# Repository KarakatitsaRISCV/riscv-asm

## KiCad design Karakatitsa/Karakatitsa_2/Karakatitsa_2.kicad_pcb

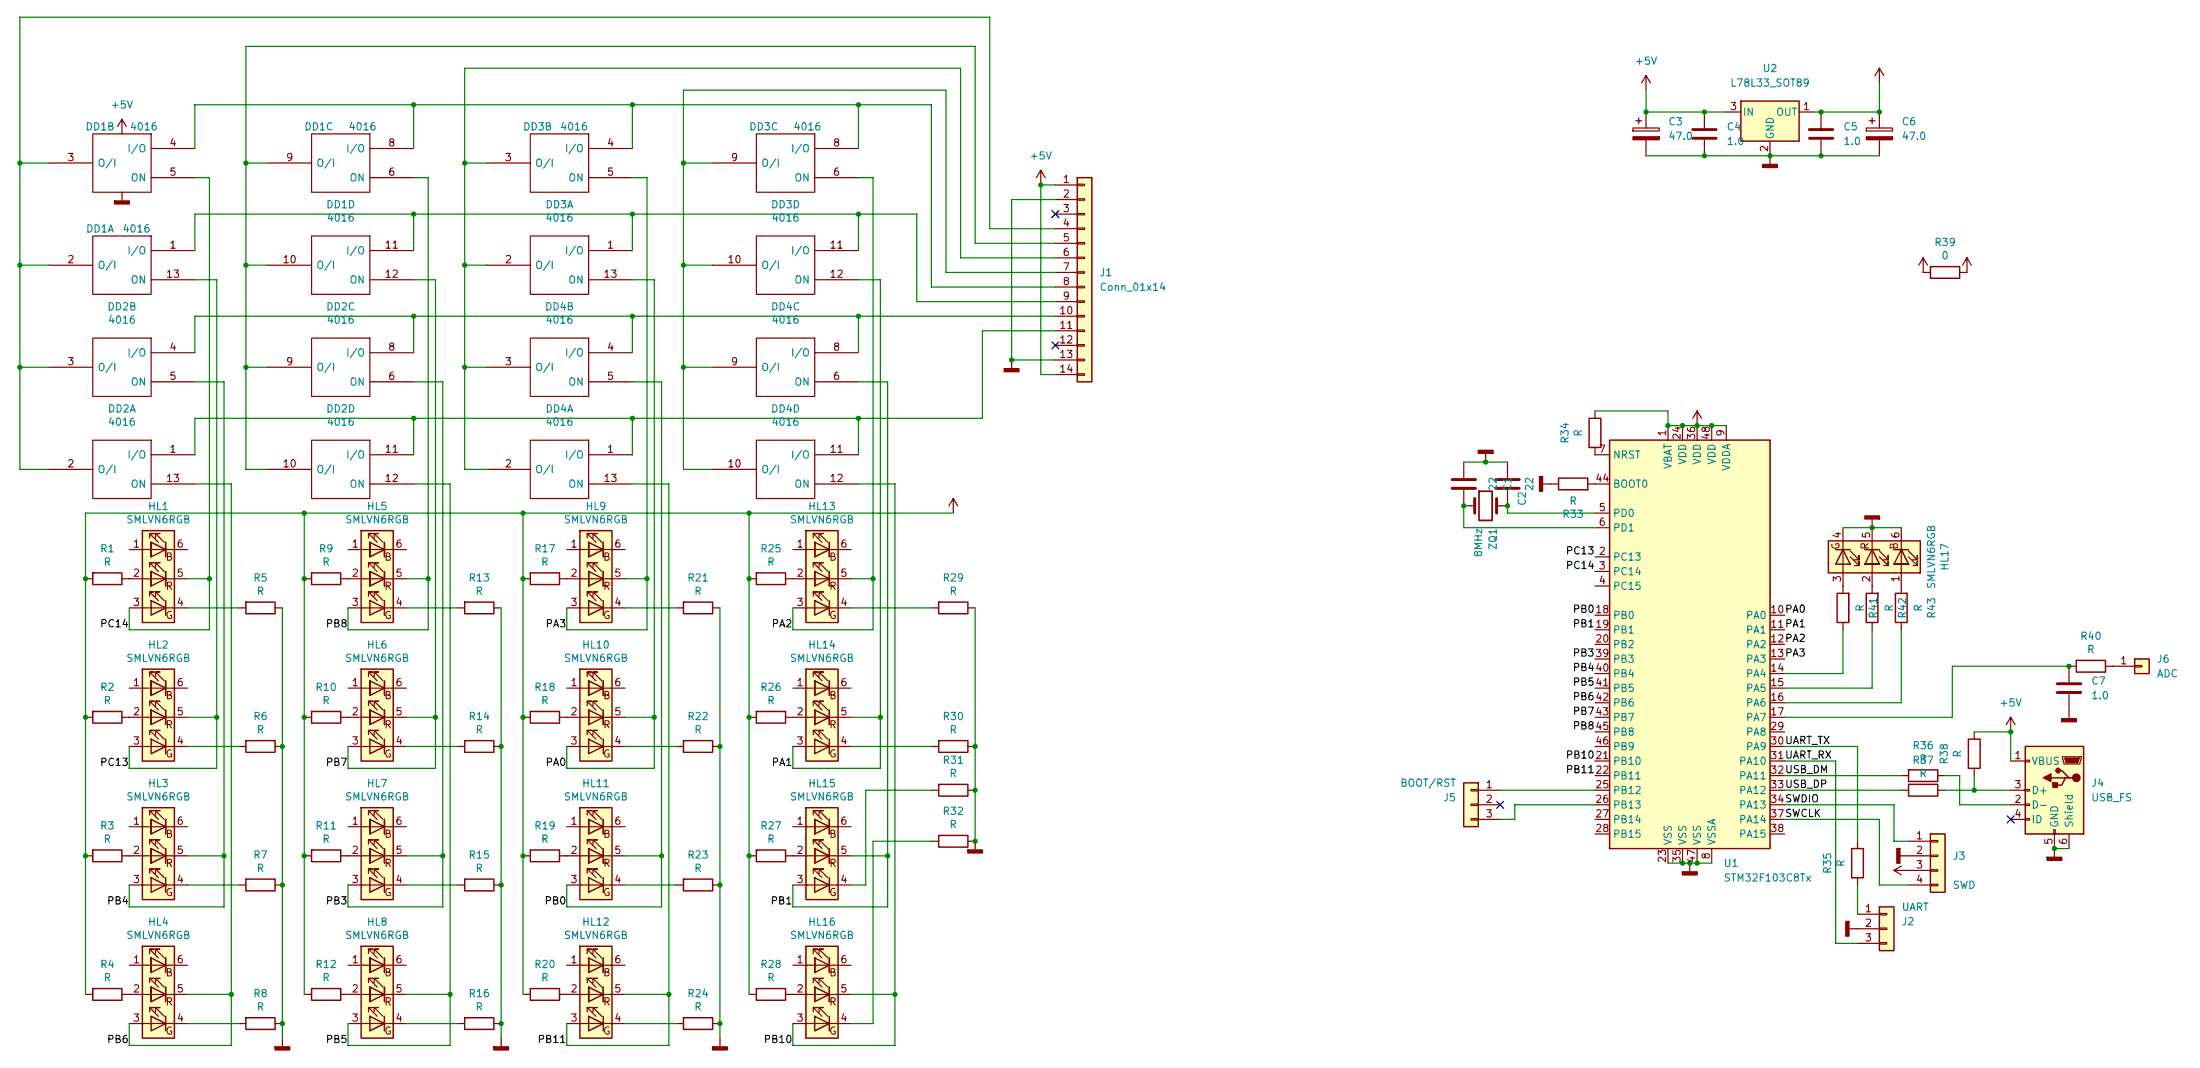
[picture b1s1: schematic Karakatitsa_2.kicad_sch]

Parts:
C1, C2: 22; C_Disc_D5.0mm_W2.5mm_P2.50mm
C3, C6: 47.0; CP_Radial_D6.3mm_P2.50mm
C4, C5, C7: 1.0; C_Disc_D7.5mm_W2.5mm_P5.00mm
DD1, DD2, DD3, DD4: 4016; DIP-14_W7.62mm_LongPads
HL1, HL2, HL3, HL4, HL5, HL6, HL7, HL8, HL9, HL10, HL11, HL12, HL13, HL14, HL15, HL16, HL17: SMLVN6RGB; LED_RGB_Cree-PLCC-6_6x5mm_P2.1mm
J1: Conn_01x14; PinSocket_1x14_P2.54mm_Horizontal
J2: UART; PinHeader_1x03_P2.54mm_Horizontal
J3: SWD; PinHeader_1x04_P2.54mm_Vertical
J4: USB_FS; USB-mini
J5: BOOT/RST; PinHeader_1x03_P2.54mm_Horizontal
J6: ADC; PinHeader_1x01_P2.54mm_Horizontal
R1, R2, R3, R4, R5, R6, R7, R8, R9, R10, R11, R12, R13, R14, R15, R16, R17, R18, R19, R20, R21, R22, R23, R24, R25, R26, R27, R28, R29, R30, R31, R32, R33, R34, R35, R36, R37, R38, R40, R41, R42, R43: R; R_0805_2012Metric
R39: 0; R_0805_2012Metric
U1: STM32F103C8Tx; LQFP-48_7x7mm_P0.5mm
U2: L78L33_SOT89; SOT-89-3
ZQ1: 8MHz; Crystal_HC49-4H_Vertical

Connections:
+5V: C3.1, C4.1, DD1.14 (Vdd), DD2.14 (Vdd), DD3.14 (Vdd), DD4.14 (Vdd), J1.1, J1.14, J4.1 (VBUS), R38.1, U2.3 (IN)
/PA0: DD3.13 (ON), HL10.3 (GA), HL10.5 (RK), U1.10 (PA0)
/PA1: DD3.12 (ON), HL14.3 (GA), HL14.5 (RK), U1.11 (PA1)
/PA2: DD3.6 (ON), HL13.3 (GA), HL13.5 (RK), U1.12 (PA2)
/PA3: DD3.5 (ON), HL9.3 (GA), HL9.5 (RK), U1.13 (PA3)
/PB0: DD4.5 (ON), HL11.3 (GA), HL11.5 (RK), U1.18 (PB0)
/PB1: DD4.6 (ON), HL15.3 (GA), HL15.5 (RK), U1.19 (PB1)
/PB3: DD2.6 (ON), HL7.3 (GA), HL7.5 (RK), U1.39 (PB3)
/PB4: DD2.5 (ON), HL3.3 (GA), HL3.5 (RK), U1.40 (PB4)
/PB5: DD2.12 (ON), HL8.3 (GA), HL8.5 (RK), U1.41 (PB5)
/PB6: DD2.13 (ON), HL4.3 (GA), HL4.5 (RK), U1.42 (PB6)
/PB7: DD1.12 (ON), HL6.3 (GA), HL6.5 (RK), U1.43 (PB7)
/PB8: DD1.6 (ON), HL5.3 (GA), HL5.5 (RK), U1.45 (PB8)
/PB10: DD4.12 (ON), HL16.3 (GA), HL16.5 (RK), U1.21 (PB10)
/PB11: DD4.13 (ON), HL12.3 (GA), HL12.5 (RK), U1.22 (PB11)
/PC13: DD1.13 (ON), HL2.3 (GA), HL2.5 (RK), U1.2 (PC13)
/PC14: DD1.5 (ON), HL1.3 (GA), HL1.5 (RK), U1.3 (PC14)
/SWCLK: J3.4, U1.37 (PA14)
/SWDIO: J3.1, U1.34 (PA13)
/UART_RX: J2.3, U1.31 (PA10)
/UART_TX: R35.1, U1.30 (PA9)
/USB_DM: R36.2, U1.32 (PA11)
/USB_DP: R37.2, U1.33 (PA12)
GNDD: C1.1, C2.1, C3.2, C4.2, C5.2, C6.2, C7.2, DD1.7 (Vss), DD2.7 (Vss), DD3.7 (Vss), DD4.7 (Vss), HL17.4 (GK), HL17.5 (RK), HL17.6 (BK), J1.2, J1.13, J2.2, J3.2, J4.5 (GND), J4.6 (Shield), R5.1, R6.1, R7.1, R8.1, R13.1, R14.1, R15.1, R16.1, R21.1, R22.1, R23.1, R24.1, R29.1, R30.1, R31.1, R32.1, R33.1, U1.8 (VSSA), U1.23 (VSS), U1.35 (VSS), U1.47 (VSS), U2.2 (GND)
unnamed: C1.2, U1.6 (PD1), ZQ1.1
unnamed: C2.2, U1.5 (PD0), ZQ1.2
unnamed: C7.1, R40.2, U1.17 (PA7)
unnamed: DD1.1 (I/O), DD1.11 (I/O), DD3.1 (I/O), DD3.11 (I/O), J1.9
unnamed: DD1.2 (O/I), DD1.3 (O/I), DD2.2 (O/I), DD2.3 (O/I), J1.4
unnamed: DD1.4 (I/O), DD1.8 (I/O), DD3.4 (I/O), DD3.8 (I/O), J1.8
unnamed: DD1.9 (O/I), DD1.10 (O/I), DD2.9 (O/I), DD2.10 (O/I), J1.5
unnamed: DD2.1 (I/O), DD2.11 (I/O), DD4.1 (I/O), DD4.11 (I/O), J1.11
unnamed: DD2.4 (I/O), DD2.8 (I/O), DD4.4 (I/O), DD4.8 (I/O), J1.10
unnamed: DD3.2 (O/I), DD3.3 (O/I), DD4.2 (O/I), DD4.3 (O/I), J1.6
unnamed: DD3.9 (O/I), DD3.10 (O/I), DD4.9 (O/I), DD4.10 (O/I), J1.7
unnamed: HL1.2 (RA), R1.1
unnamed: HL1.4 (GK), R5.2
unnamed: HL2.2 (RA), R2.1
unnamed: HL2.4 (GK), R6.2
unnamed: HL3.2 (RA), R3.1
unnamed: HL3.4 (GK), R7.2
unnamed: HL4.2 (RA), R4.1
unnamed: HL4.4 (GK), R8.2
unnamed: HL5.2 (RA), R9.1
unnamed: HL5.4 (GK), R13.2
unnamed: HL6.2 (RA), R10.1
unnamed: HL6.4 (GK), R14.2
unnamed: HL7.2 (RA), R11.1
unnamed: HL7.4 (GK), R15.2
unnamed: HL8.2 (RA), R12.1
unnamed: HL8.4 (GK), R16.2
unnamed: HL9.2 (RA), R17.1
unnamed: HL9.4 (GK), R21.2
unnamed: HL10.2 (RA), R18.1
unnamed: HL10.4 (GK), R22.2
unnamed: HL11.2 (RA), R19.1
unnamed: HL11.4 (GK), R23.2
unnamed: HL12.2 (RA), R20.1
unnamed: HL12.4 (GK), R24.2
unnamed: HL13.2 (RA), R25.1
unnamed: HL13.4 (GK), R29.2
unnamed: HL14.2 (RA), R26.1
unnamed: HL14.4 (GK), R30.2
unnamed: HL15.2 (RA), R27.1
unnamed: HL15.4 (GK), R31.2
unnamed: HL16.2 (RA), R28.1
unnamed: HL16.4 (GK), R32.2
unnamed: HL17.1 (BA), R43.2
unnamed: HL17.2 (RA), R42.2
unnamed: HL17.3 (GA), R41.2
unnamed: J2.1, R35.2
unnamed: J4.2 (D-), R36.1
unnamed: J4.3 (D+), R37.1, R38.2
unnamed: J5.1, U1.25 (PB12)
unnamed: J5.3, U1.26 (PB13)
unnamed: J6.1, R40.1
unnamed: R33.2, U1.44 (BOOT0)
unnamed: R34.2, U1.7 (NRST)
unnamed: R41.1, U1.14 (PA4)
unnamed: R42.1, U1.15 (PA5)
unnamed: R43.1, U1.16 (PA6)
VCC: C5.1, C6.1, J3.3, R1.2, R2.2, R3.2, R4.2, R9.2, R10.2, R11.2, R12.2, R17.2, R18.2, R19.2, R20.2, R25.2, R26.2, R27.2, R28.2, R34.1, R39.1, R39.2, U1.1 (VBAT), U1.9 (VDDA), U1.24 (VDD), U1.36 (VDD), U1.48 (VDD), U2.1 (OUT)

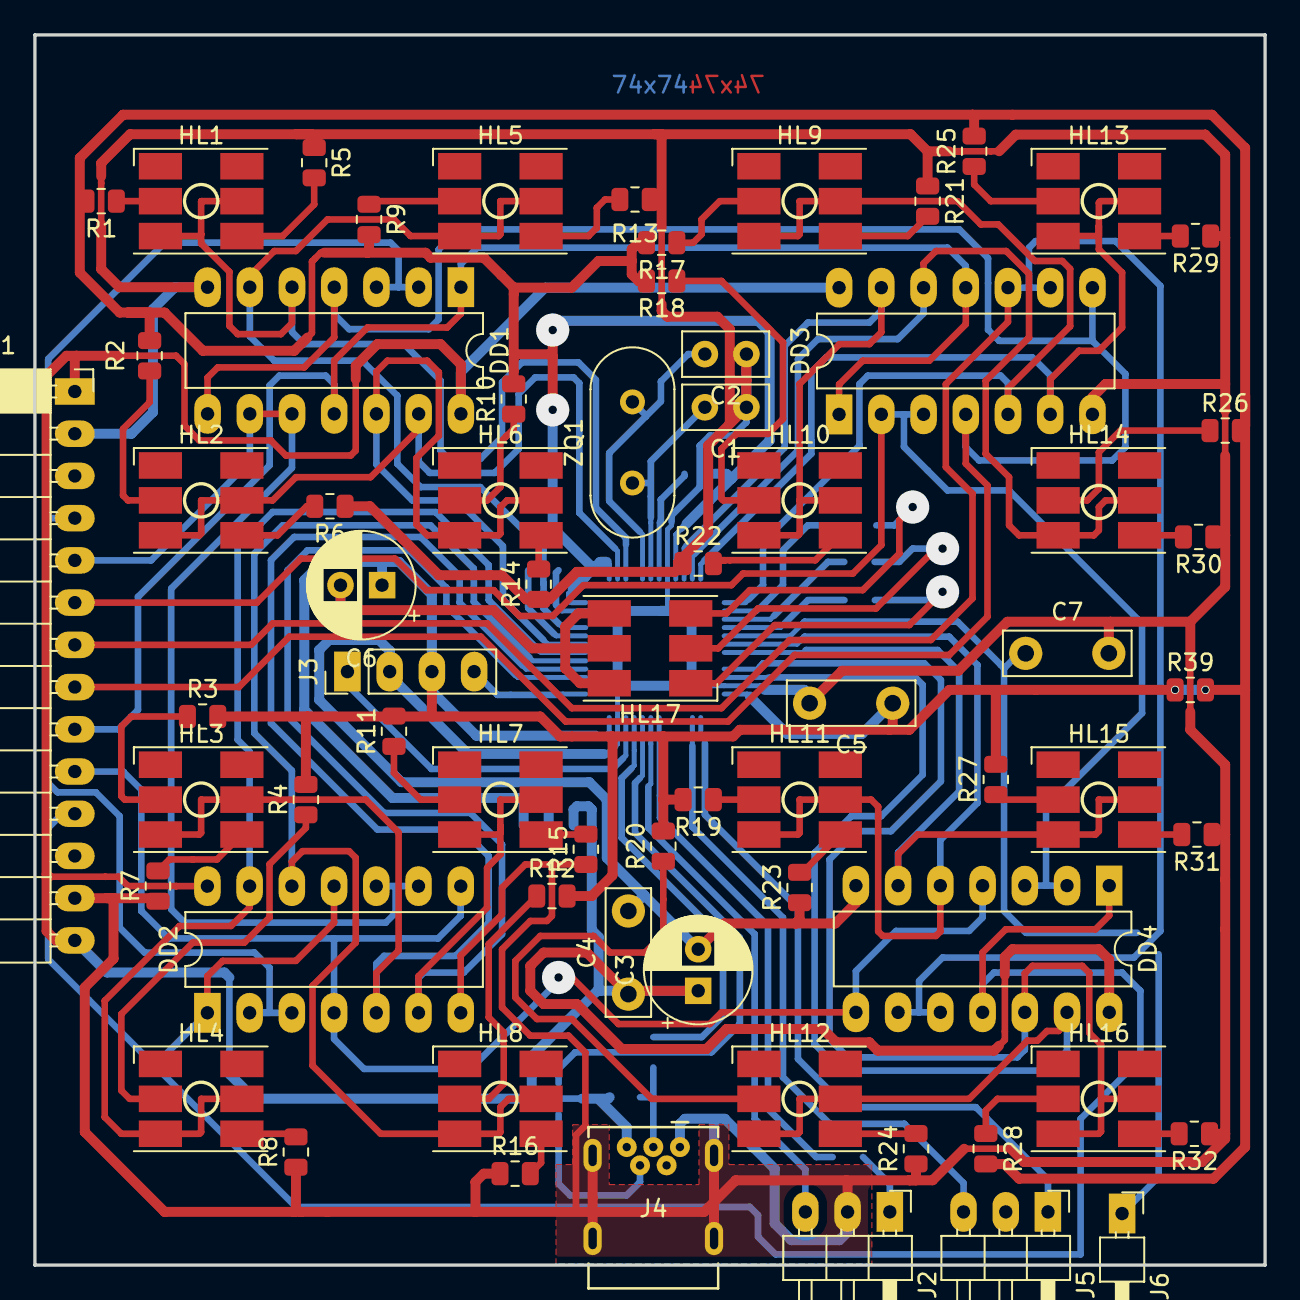
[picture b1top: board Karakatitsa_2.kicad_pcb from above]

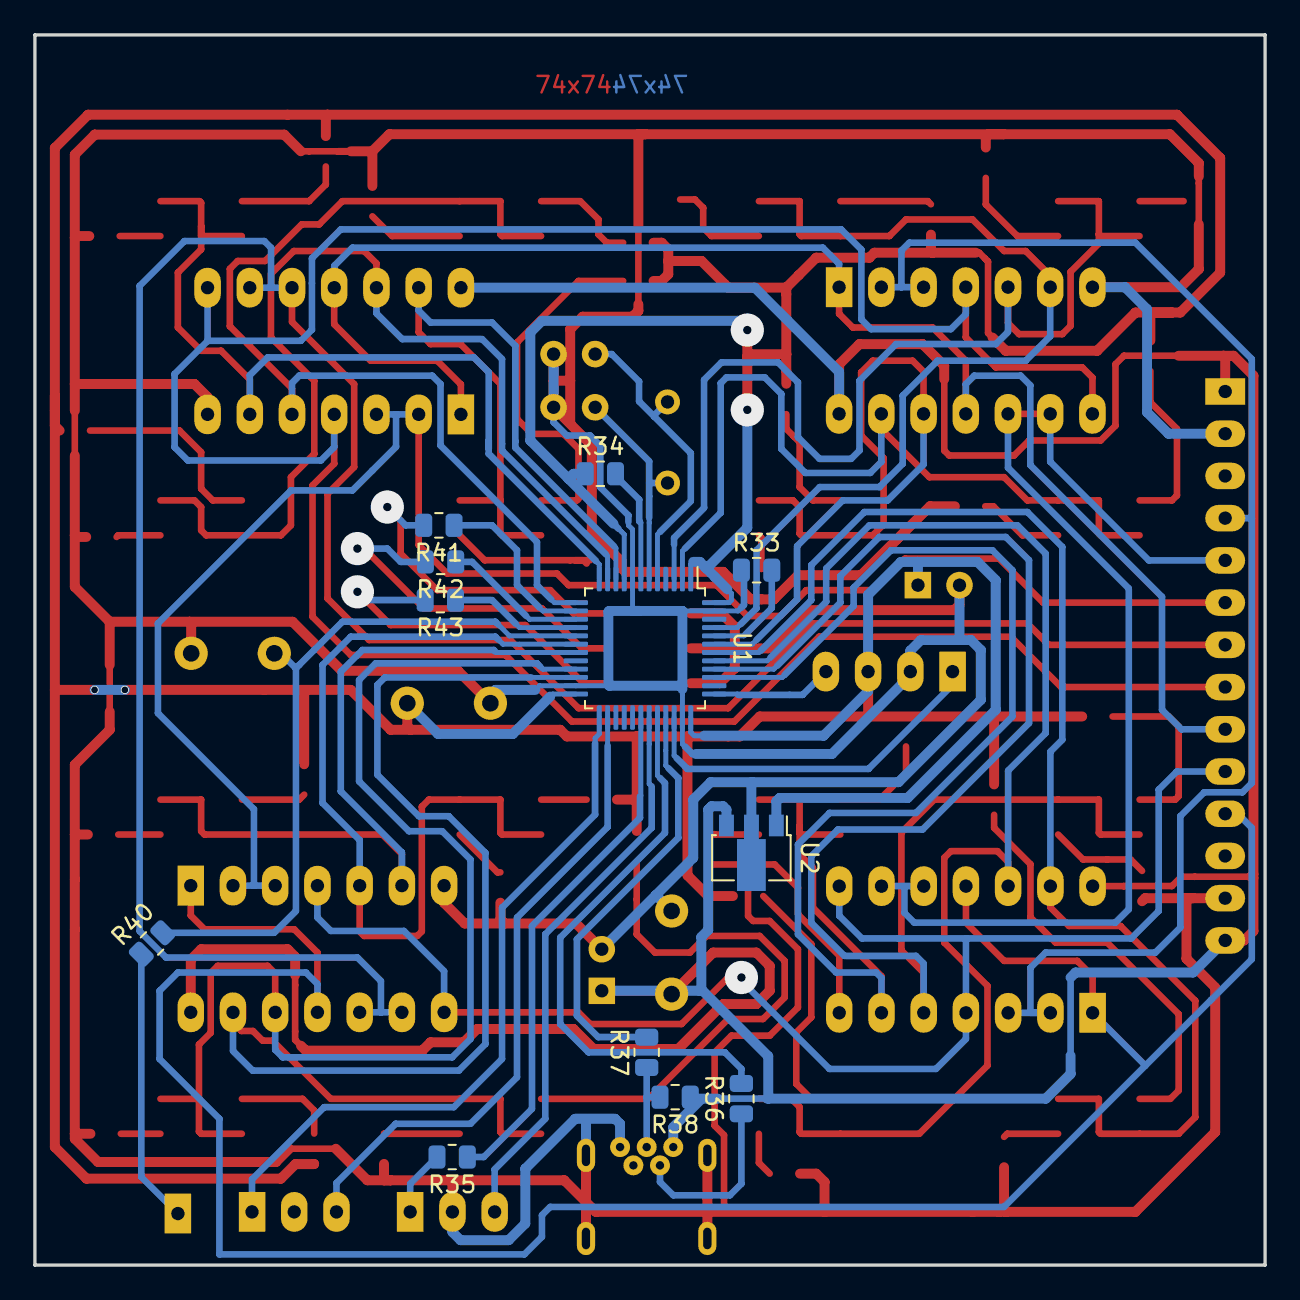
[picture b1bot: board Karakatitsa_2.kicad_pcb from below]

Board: 2 copper layers, 74.0 x 74.0 mm, 80 parts (12 on the bottom side), 82 nets.

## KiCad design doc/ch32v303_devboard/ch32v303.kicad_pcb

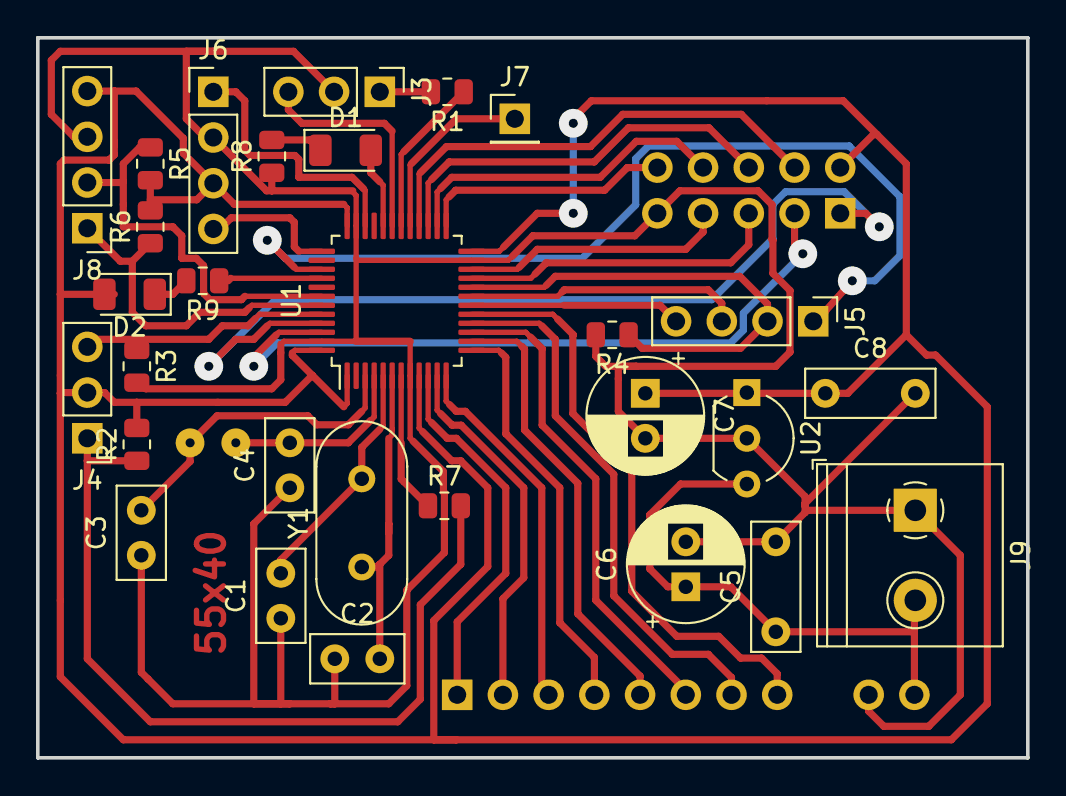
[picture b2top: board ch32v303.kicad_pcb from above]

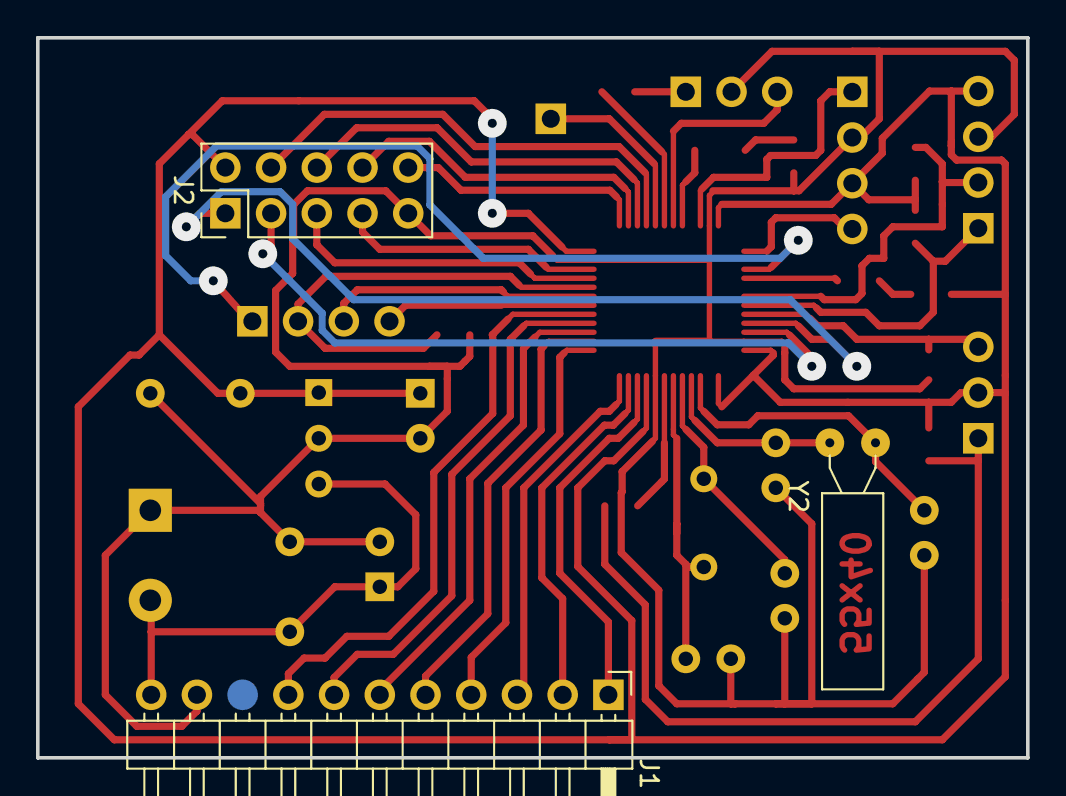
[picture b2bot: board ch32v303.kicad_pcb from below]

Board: 2 copper layers, 55.0 x 40.0 mm, 32 parts (3 on the bottom side), 42 nets.

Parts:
C1, C2, C3, C4: 22; C_Disc_D5.0mm_W2.5mm_P2.50mm
C5, C8: 0.1; C_Disc_D7.0mm_W2.5mm_P5.00mm
C6, C7: 100.0; CP_Radial_D6.3mm_P2.50mm
D1, D2: LED; LED_1206_3216Metric
J1: KBD; PinHeader_1x11_P2.54mm_Horizontal
J2: 7SEG_SEG; PinHeader_2x05_P2.54mm_Vertical
J3: UART; PinHeader_1x03_P2.54mm_Vertical
J4: BOOT/RST; PinHeader_1x03_P2.54mm_Vertical
J5: 7SEG_SEG; PinHeader_1x04_P2.54mm_Vertical
J6: SWD; PinHeader_1x04_P2.54mm_Vertical
J7: PWM; PinHeader_1x01_P2.54mm_Vertical
J8: I2C; PinHeader_1x04_P2.54mm_Vertical
J9: PWR; TerminalBlock_Philmore_TB132_1x02_P5.00mm_Horizontal
R1, R2, R3, R4, R5, R6, R8, R9: 1k; R_0805_2012Metric
R7: 0; R_0805_2012Metric
U1: STM32F103C8Tx; LQFP-48_7x7mm_P0.5mm
U2: L78L33_TO92; TO-92_Inline_Wide
Y1: 8MHz; Crystal_HC18-U_Vertical
Y2: 32k; Crystal_AT310_D3.0mm_L10.0mm_Horizontal

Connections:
+5V: C5.1, C6.1, J1.11, J9.2, U2.3 (VI)
/BOOT: J4.3, R3.1, U1.44 (BOOT0)
/RST: J4.1, R2.1, R7.2
/RX: J3.3, U1.31 (PA10)
/SCL: J8.2, R5.1, U1.42 (PB6)
/SDA: J8.1, R6.1, U1.43 (PB7)
/SWCLK: J6.4, U1.37 (PA14)
/SWDIO: J6.1, U1.34 (PA13)
/TX: R1.1, U1.30 (PA9)
GNDD: C1.1, C2.1, C3.1, C4.1, C5.2, C6.2, C7.2, C8.2, J1.10, J2.9, J3.2, J6.2, J8.3, J9.1, R3.2, R4.2, R8.1, U1.8 (VSSA), U1.23 (VSS), U1.35 (VSS), U1.47 (VSS), U2.2 (GND)
unnamed: D1.2 (A), U1.32 (PA11)
unnamed: D1.1 (K), R8.2
unnamed: D2.1 (K), R9.2
unnamed: J1.1, U1.10 (PA0)
unnamed: J1.2, U1.11 (PA1)
unnamed: J1.3, U1.12 (PA2)
unnamed: J1.4, U1.13 (PA3)
unnamed: J1.5, U1.14 (PA4)
unnamed: J1.6, U1.15 (PA5)
unnamed: J1.7, U1.16 (PA6)
unnamed: J1.8, U1.17 (PA7)
unnamed: J2.1, U1.45 (PB8)
unnamed: J2.3, U1.46 (PB9)
unnamed: J2.4, U1.28 (PB15)
unnamed: J2.5, U1.21 (PB10)
unnamed: J2.6, U1.27 (PB14)
unnamed: J2.7, U1.22 (PB11)
unnamed: J2.8, U1.26 (PB13)
unnamed: J2.10, U1.25 (PB12)
unnamed: J3.1, R1.2
unnamed: J5.1, U1.39 (PB3)
unnamed: J5.2, R4.1, U1.20 (PB2)
unnamed: J5.3, U1.19 (PB1)
unnamed: J5.4, U1.18 (PB0)
unnamed: J7.1, U1.29 (PA8)
unnamed: R7.1, U1.7 (NRST)
unnamed: R9.1, U1.40 (PB4)
unnamed: C3.2, U1.3 (PC14), Y2.2
unnamed: C4.2, U1.4 (PC15), Y2.1
unnamed: C1.2, U1.5 (PD0), Y1.2
unnamed: C2.2, U1.6 (PD1), Y1.1
VCC: C7.1, C8.1, D2.2 (A), J2.2, J4.2, J6.3, J8.4, R2.2, R5.2, R6.2, U1.1 (VBAT), U1.9 (VDDA), U1.24 (VDD), U1.36 (VDD), U1.48 (VDD), U2.1 (VO)

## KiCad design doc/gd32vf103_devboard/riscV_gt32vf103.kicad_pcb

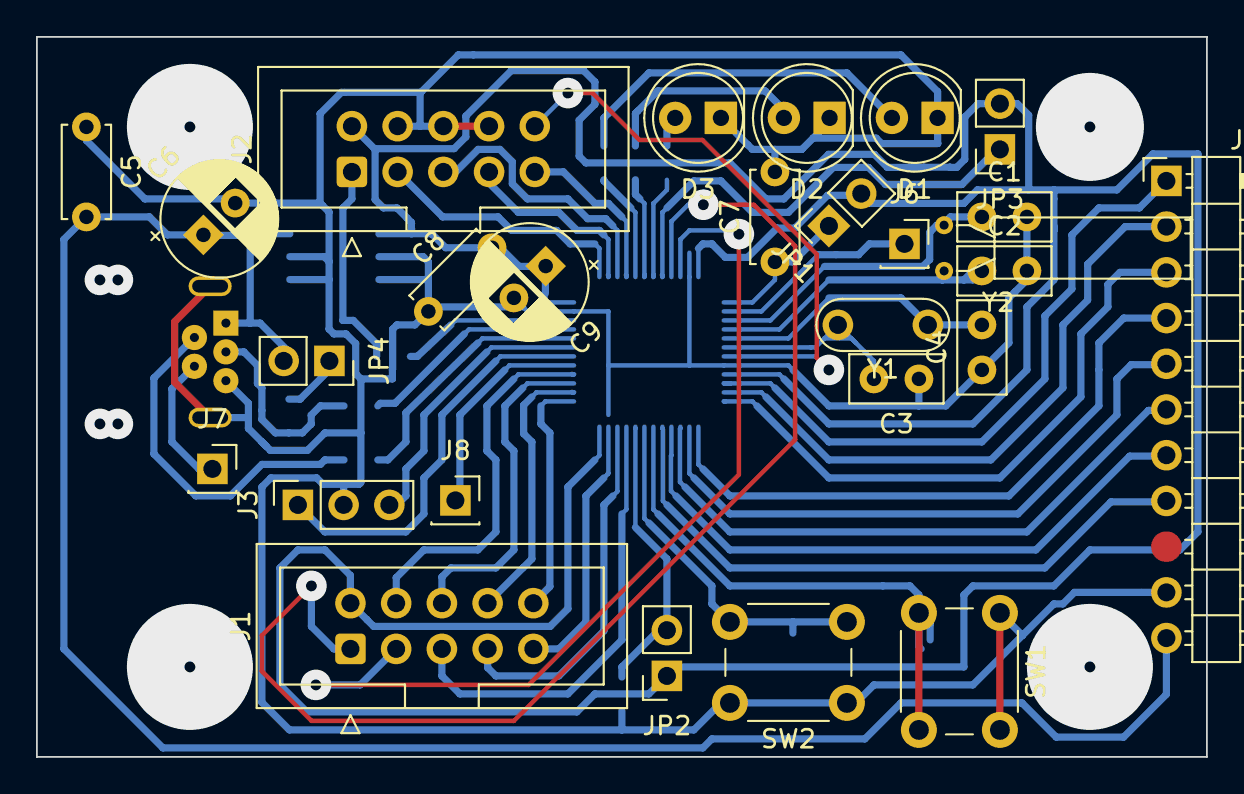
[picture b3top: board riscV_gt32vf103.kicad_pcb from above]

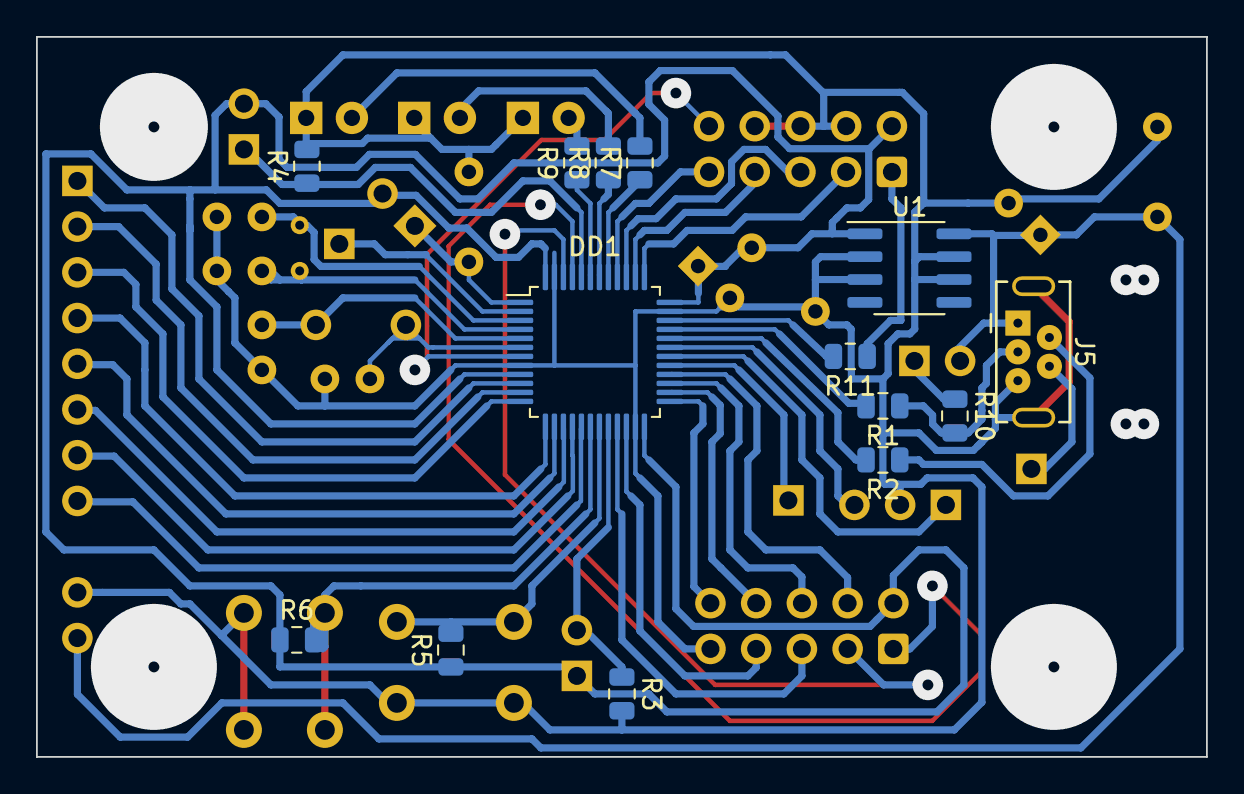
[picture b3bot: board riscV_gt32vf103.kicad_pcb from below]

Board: 2 copper layers, 65.0 x 40.0 mm, 41 parts (14 on the bottom side), 51 nets.

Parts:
C1, C2, C3, C4: C; C_Disc_D5.0mm_W2.5mm_P2.50mm
C5, C7, C8: C; C_Disc_D5.0mm_W2.5mm_P5.00mm
C6, C9: CP; CP_Radial_D6.3mm_P2.50mm
D1, D2, D3: LED; LED_D5.0mm_Clear
DD1: STM32F103CBTx; LQFP-48_7x7mm_P0.5mm
J1: PORTB; IDC-Header_2x05_P2.54mm_Vertical
J2: JTAG; IDC-Header_2x05_P2.54mm_Vertical
J3: UART; PinSocket_1x03_P2.54mm_Vertical
J4: PORTA; PinHeader_1x11_P2.54mm_Horizontal
J5: USB_B_Mini; USB_Mini-B_Tensility_54-00023_Vertical
J6: PC13; PinSocket_1x01_P2.54mm_Vertical
J7: USB_ID; PinSocket_1x01_P2.54mm_Vertical
J8: PA8; PinSocket_1x01_P2.54mm_Vertical
JP1: Jumper; PinSocket_1x02_P2.54mm_Vertical
JP2: BOOT1; PinSocket_1x02_P2.54mm_Vertical
JP3: BOOT0; PinSocket_1x02_P2.54mm_Vertical
JP4: usb_pup; PinSocket_1x02_P2.54mm_Vertical
R1, R2, R3, R4, R5, R6, R7, R8, R9, R10, R11: R; R_0805_2012Metric
SW1, SW2: SW_Push; SW_PUSH_6mm_H8mm
U1: L78L33_SO8; SOIC-8_3.9x4.9mm_P1.27mm
Y1: HSE; Resonator-2Pin_W7.0mm_H2.5mm
Y2: 32k; Crystal_AT310_D3.0mm_L10.0mm_Horizontal

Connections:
+5V: C5.2, C6.1, J4.11, J5.1, JP4.2, U1.8
GNDD: C1.2, C2.2, C3.1, C4.1, C5.1, C6.2, C7.2, C8.1, C9.2, D1.1, D2.1, D3.1, DD1.8, DD1.23, DD1.35, DD1.47, J1.9, J2.4, J2.6, J2.8, J3.2, J4.10, J5.5, J5.6, R3.2, R4.2, SW1.1, SW2.1, U1.2, U1.3, U1.6, U1.7
unnamed: C1.1, DD1.3, Y2.2
unnamed: C2.1, DD1.4, Y2.1
unnamed: C3.2, DD1.6, Y1.2
unnamed: C4.2, DD1.5, Y1.1
unnamed: C7.1, DD1.1, JP1.1
unnamed: D1.2, R7.2
unnamed: D2.2, R8.2
unnamed: D3.2, R9.2
unnamed: DD1.2, J6.1
unnamed: DD1.7, J2.10
unnamed: DD1.10, J4.1
unnamed: DD1.11, J4.2
unnamed: DD1.12, J4.3
unnamed: DD1.13, J4.4
unnamed: DD1.14, J4.5
unnamed: DD1.15, J4.6
unnamed: DD1.16, J4.7
unnamed: DD1.17, J4.8
unnamed: DD1.18, R6.2, SW1.2
unnamed: DD1.19, R5.2, SW2.2
unnamed: DD1.20, JP2.2, R3.1
unnamed: DD1.21, J1.5
unnamed: DD1.22, J1.7
unnamed: DD1.25, J1.10
unnamed: DD1.26, J1.8
unnamed: DD1.27, J1.6
unnamed: DD1.28, J1.4
unnamed: DD1.29, J8.1
unnamed: DD1.30, J3.1
unnamed: DD1.31, J3.3
unnamed: DD1.32, R2.2
unnamed: DD1.33, R1.2
unnamed: DD1.34, R11.2
unnamed: DD1.37, J2.3
unnamed: DD1.38, J2.7
unnamed: DD1.39, J2.5
unnamed: DD1.40, J2.9
unnamed: DD1.41, R7.1
unnamed: DD1.42, R8.1
unnamed: DD1.43, R9.1
unnamed: DD1.44, JP3.1, R4.1
unnamed: DD1.45, J1.1
unnamed: DD1.46, J1.3
unnamed: J2.1, R11.1
unnamed: J5.2, R2.1
unnamed: J5.3, R1.1, R10.2
unnamed: J5.4, J7.1
unnamed: JP4.1, R10.1
VCC: C8.2, C9.1, DD1.9, DD1.24, DD1.36, DD1.48, J1.2, J2.2, JP1.2, JP2.1, JP3.2, R5.1, R6.1, U1.1

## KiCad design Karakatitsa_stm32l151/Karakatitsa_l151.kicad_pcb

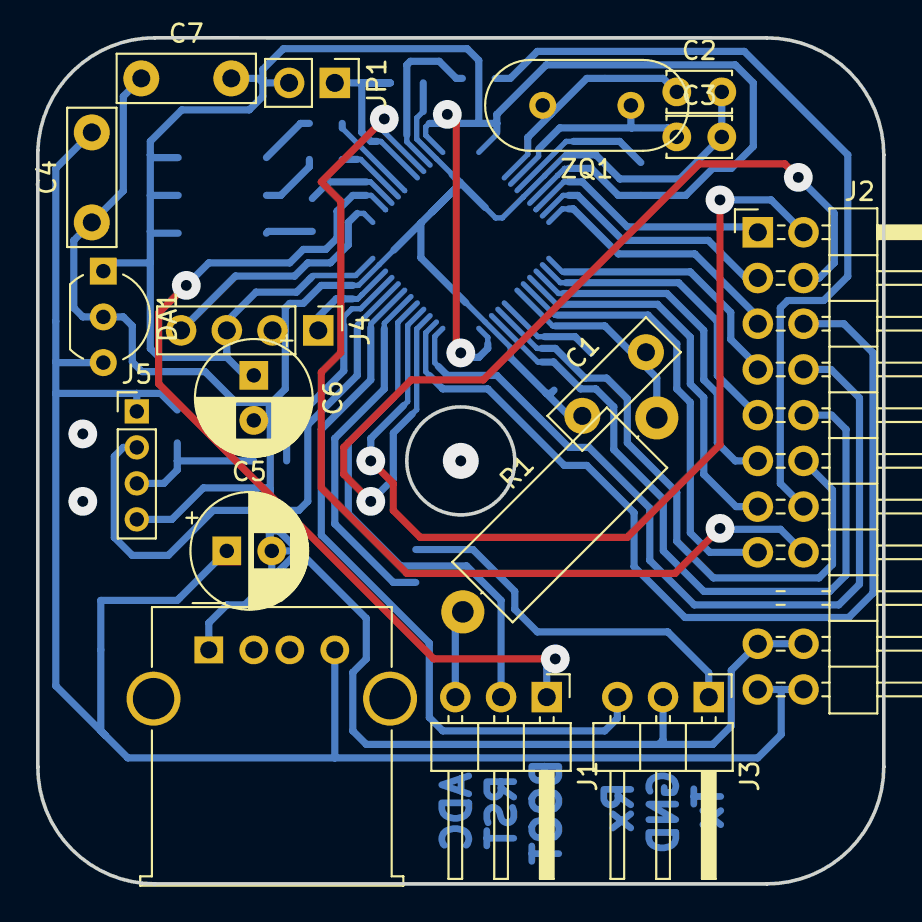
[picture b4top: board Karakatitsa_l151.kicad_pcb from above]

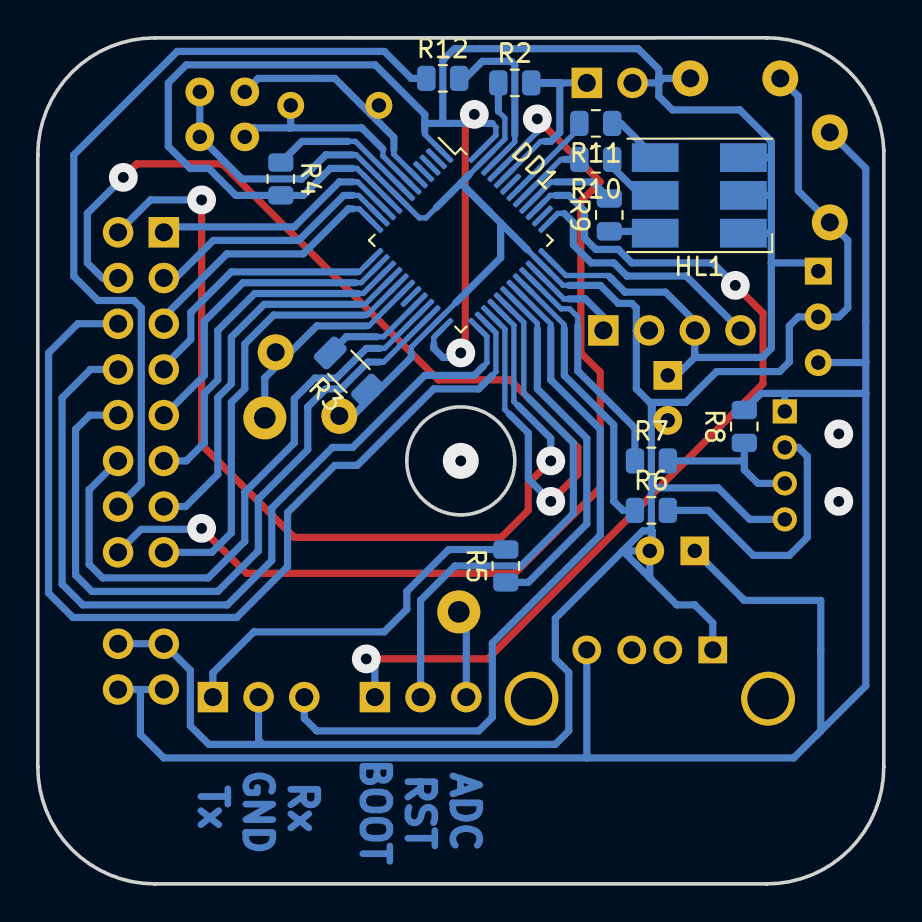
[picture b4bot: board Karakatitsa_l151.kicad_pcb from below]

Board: 2 copper layers, 47.0 x 47.0 mm, 30 parts (13 on the bottom side), 44 nets.

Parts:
C1: 10000; C_Disc_D7.5mm_W2.5mm_P5.00mm
C2, C3: 22; C_Disc_D3.4mm_W2.1mm_P2.50mm
C4, C7: 1.0; C_Disc_D7.5mm_W2.5mm_P5.00mm
C5, C6: 47.0; CP_Radial_D6.3mm_P2.50mm
DA1: L78L33; TO-92_Inline_Wide
DD1: STM32L151C8Tx; LQFP-48_7x7mm_P0.5mm
HL1: SMLVN6RGB; LED_RGB_Cree-PLCC-6_6x5mm_P2.1mm
J1: CTL; PinHeader_1x03_P2.54mm_Horizontal
J2: KBD; PinHeader_2x11_P2.54mm_Horizontal
J3: UART; PinHeader_1x03_P2.54mm_Horizontal
J4: SWD; PinHeader_1x04_P2.54mm_Vertical
J5: USB_B_Mini; PinHeader_1x04_P2.00mm_Vertical
J6: PWR; USB_A_Molex_67643_Horizontal
JP1: BOOT0; PinHeader_1x02_P2.54mm_Vertical
R1: 1.1k; R_Axial_DIN0414_L11.9mm_D4.5mm_P15.24mm_Horizontal
R2, R4: 10k; R_0805_2012Metric
R3: 10k; R_1206_3216Metric
R5, R9, R10, R11: 680; R_0805_2012Metric
R6, R7: 68; R_0805_2012Metric
R8: 1.5k; R_0805_2012Metric
R12: Fuse; R_0805_2012Metric
ZQ1: 8 MHz; Crystal_HC18-U_Vertical

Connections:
+3V3: C6.1, C7.2, DA1.1 (VO), DD1.1 (VLCD), DD1.9 (VDDA), DD1.24 (VDD), DD1.36 (VDD), DD1.48 (VDD), HL1.1 (BA), HL1.2 (RA), HL1.3 (GA), J4.3, JP1.2 (B), R4.2
+5V: C4.2, C5.1, DA1.3 (VI), J2.21, J2.22, J5.1 (VBUS), J6.4, R8.2
/ADC: J1.3, R1.1
/BLED: DD1.40 (PB4), R9.2
/BOOT: DD1.39 (PB3), J1.1
/GLED: DD1.42 (PB6), R11.2
/PB8: DD1.45 (PB8), J2.16
/PB9: DD1.46 (PB9), R12.2
/PB10: DD1.21 (PB10), J2.12
/PB11: DD1.22 (PB11), J2.10
/PB12: DD1.25 (PB12), J2.8
/PB13: DD1.26 (PB13), J2.6
/PB14: DD1.27 (PB14), J2.4
/PB15: DD1.28 (PB15), J2.2
/RLED: DD1.41 (PB5), R10.2
/RST: DD1.29 (PA8), J1.2
/RX: DD1.31 (PA10), J3.3
/SWCLK: DD1.37 (PA14), J4.4
/SWDIO: DD1.34 (PA13), J4.1
/TX: DD1.30 (PA9), R5.1
GNDD: C1.1, C2.2, C3.2, C4.1, C5.2, C6.2, C7.1, DA1.2 (GND), DD1.8 (VSSA), DD1.23 (VSS), DD1.35 (VSS), DD1.47 (VSS), J2.19, J2.20, J3.2, J4.2, J5.4 (ID), J6.1, R2.1, R3.1
unnamed: C1.2, DD1.18 (PB0), R1.2
unnamed: C2.1, DD1.5 (PH0), ZQ1.2
unnamed: C3.1, DD1.6 (PH1), ZQ1.1
unnamed: DD1.7 (NRST), R4.1
unnamed: DD1.10 (PA0), J2.1
unnamed: DD1.11 (PA1), J2.3
unnamed: DD1.12 (PA2), J2.5
unnamed: DD1.13 (PA3), J2.7
unnamed: DD1.14 (PA4), J2.9
unnamed: DD1.15 (PA5), J2.11
unnamed: DD1.16 (PA6), J2.13
unnamed: DD1.17 (PA7), J2.15
unnamed: DD1.20 (PB2), R3.2
unnamed: DD1.32 (PA11), R6.1
unnamed: DD1.33 (PA12), R7.1
unnamed: DD1.44 (BOOT0), JP1.1 (A), R2.2
unnamed: HL1.4 (GK), R11.1
unnamed: HL1.5 (RK), R10.1
unnamed: HL1.6 (BK), R9.1
unnamed: J2.14, R12.1
unnamed: J3.1, R5.2
unnamed: J5.2 (D-), R6.2
unnamed: J5.3 (D+), R7.2, R8.1

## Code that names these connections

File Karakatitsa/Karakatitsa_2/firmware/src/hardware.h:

#ifndef __HARDWARE_H__
#define __HARDWARE_H__

//TIM2 -> USB_MIC / ADC

#define GLED  A,4,1,GPIO_PP50
#define RLED  A,5,1,GPIO_PP50
#define BLED  A,6,1,GPIO_PP50

#define USB_DP	A,12,1,GPIO_HIZ

#define UART_TX A,9, GPIO_APP50
#define UART_RX A,10,GPIO_HIZ

//#define USBR	B,2,0,GPIO_PP50
#define ADC_IN  A,7,7,GPIO_ADC
 
#define RESET   B,12,0,GPIO_PP50
#define BOOT0   B,13,1,GPIO_PP50

// KEY matrix
#define KBD_0	C,14,1,GPIO_PP50
#define KBD_1	B,8,1,GPIO_PP50
#define KBD_2	A,3,1,GPIO_PP50
#define KBD_3	A,2,1,GPIO_PP50

#define KBD_4	C,13,1,GPIO_PP50
#define KBD_5	B,7,1,GPIO_PP50
#define KBD_6	A,0,1,GPIO_PP50
#define KBD_7	A,1,1,GPIO_PP50

#define KBD_8	B,4,1,GPIO_PP50
#define KBD_9	B,3,1,GPIO_PP50
#define KBD_10	B,0,1,GPIO_PP50
#define KBD_11	B,1,1,GPIO_PP50

#define KBD_12	B,6,1,GPIO_PP50
#define KBD_13	B,5,1,GPIO_PP50
#define KBD_14	B,11,1,GPIO_PP50
#define KBD_15	B,10,1,GPIO_PP50

#define jtag_disable() do{\
  RCC->APB2ENR |= RCC_APB2ENR_AFIOEN;\
  AFIO->MAPR = (AFIO->MAPR &~AFIO_MAPR_SWJ_CFG) | AFIO_MAPR_SWJ_CFG_JTAGDISABLE;\
}while(0)

#include "pinmacro.h"
  
//------ USB -------------------
//PMA_size = 128
//EP0_size = 8

//Custom HID
//define ENDP_HID (none)
// /dev/ttyACM0 - TTY
#define ENDP_TTY_IN	1
#define ENDP_TTY_OUT	1
#define ENDP_TTY_SIZE	32 //->64
// /dev/ttyACM1 - PROGR
#define ENDP_PROG_IN	2
#define ENDP_PROG_OUT	2
#define ENDP_PROG_SIZE	32 //->64
//UART1+2 - common interrupt endpoint (placeholder)
#define ENDP_TTY_CTL	3
#define ENDP_PROG_CTL	4
#define ENDP_CTL_SIZE	8 //->8
//Audio microphone (ADC on PB0)
#define ENDP_MIC	5
#define ENDP_MIC_SIZE	100 //->200
// 128 + 8 + 2*32 + 2*32 + 2*8 + 2*100

#define interface_hid	0, 1
#define interface_tty	1, 2
#define interface_progr	3, 2
#define interface_mic	5, 2
#define interface_count	7

#define ifnum(x) _marg1(x)
#define ifcnt(x) _marg2(x)

#endif

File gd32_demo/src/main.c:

#include <stdint.h>
#include "gd32vf103.h"
#include "interrupt_util.h"
#include "pinmacro.h"
#include "hardware.h"

uint32_t SystemCoreClock = 8000000;
//#define F_CPU	8000000
#define F_CPU	108000000

void sleep(uint32_t i){
  while(i--)asm volatile("nop");
}

void uart_putc(char c){
  while(! (USART_STAT(USART0) & USART_STAT_TBE) ){}
  USART_DATA(USART0) = c;
}
void uart_u32(uint32_t val){
  char buf[11];
  char *ch = &buf[10];
  ch[0] = 0;
  do{
    *(--ch) = (val % 10) + '0';
    val /= 10;
  }while(val);
  while(ch[0] != 0){
    uart_putc(ch[0]);
    ch++;
  }
  uart_putc('\r'); uart_putc('\n');
}
void uart_b16(uint16_t val){
  for(uint16_t mask = 0x8000; mask!=0; mask>>=1){
    if(mask == 0x0080)uart_putc(' ');
    if(val & mask)uart_putc('1'); else uart_putc('0');
  }
  uart_putc('\r'); uart_putc('\n');
}


#define ADDR_0	A,13,1,GPIO_PP50
#define ADDR_1	A,14,1,GPIO_PP50
#define ADDR_2	A,15,1,GPIO_PP50
#define ADDR_3	B,3,1,GPIO_PP50

void led_addr(uint8_t addr){
  if(addr & 1)GPO_ON(ADDR_0); else GPO_OFF(ADDR_0);
  if(addr & 2)GPO_ON(ADDR_1); else GPO_OFF(ADDR_1);
  if(addr & 4)GPO_ON(ADDR_2); else GPO_OFF(ADDR_2);
  if(addr & 8)GPO_ON(ADDR_3); else GPO_OFF(ADDR_3);
}

#define SEG_A	(1<<0)
#define SEG_B	(1<<1)
#define SEG_C	(1<<2)
#define SEG_D	(1<<3)
#define SEG_E	(1<<4)
#define SEG_F	(1<<5)
#define SEG_G	(1<<6)
#define SEG_DOT	(1<<7)

#define NUM_0	(SEG_A | SEG_B | SEG_C | SEG_D | SEG_E | SEG_F)
#define NUM_1	(SEG_B | SEG_C)
#define NUM_2	(SEG_A | SEG_B | SEG_D | SEG_E | SEG_G)
#define NUM_3	(SEG_A | SEG_B | SEG_C | SEG_D | SEG_G)
#define NUM_4	(SEG_B | SEG_C | SEG_F | SEG_G)
#define NUM_5	(SEG_A | SEG_C | SEG_D | SEG_F | SEG_G)
#define NUM_6	(SEG_A | SEG_C | SEG_D | SEG_E | SEG_F | SEG_G)
#define NUM_7	(SEG_A | SEG_B | SEG_C)
#define NUM_8	(SEG_A | SEG_B | SEG_C | SEG_D | SEG_E | SEG_F | SEG_G)
#define NUM_9	(SEG_A | SEG_B | SEG_C | SEG_D | SEG_F | SEG_G)
#define NUM_A	(SEG_A | SEG_B | SEG_C | SEG_E | SEG_F | SEG_G)
#define NUM_B	(SEG_C | SEG_D | SEG_E | SEG_F | SEG_G)
#define NUM_C	(SEG_A | SEG_D | SEG_E | SEG_F)
#define NUM_D	(SEG_B | SEG_C | SEG_D | SEG_E | SEG_G)
#define NUM_E	(SEG_A | SEG_D | SEG_E | SEG_F | SEG_G)
#define NUM_F	(SEG_A | SEG_E | SEG_F | SEG_G)
const uint8_t seg_code[] = {NUM_0, NUM_1, NUM_2, NUM_3, NUM_4, NUM_5, NUM_6, NUM_7, NUM_8, NUM_9, NUM_A, NUM_B, NUM_C, NUM_D, NUM_E, NUM_F};

uint8_t screen[11] = {
  0b01100110,
  0b01100110,
  0b00000000,
  0b00000000,
  0b00000000,
  0b10000001,
  0b01000010,
  0b00111100,
  
  NUM_0, NUM_0, NUM_0
};

void screen_update(){
  static uint8_t cnt = 0;
  GPIO_OCTL(GPIOB) &= 0x00FF;
  led_addr(cnt);
  GPIO_OCTL(GPIOB) |= (screen[cnt] << 8);
  cnt++;
  if(cnt > 11)cnt = 0;
}

void screen_init(){
  AFIO_PCF0 = (AFIO_PCF0 &~(0b111<<24)) | (0b100 << 24);
  GPIO_config(ADDR_0); GPIO_config(ADDR_1); GPIO_config(ADDR_2); GPIO_config(ADDR_3);
  GPIO_CTL1(GPIOB) = 0x11111111 * GPIO_PP50;
}



uint16_t kbd_update(){
  static uint16_t status_res = 0;
  static uint16_t status = 0;
  static uint16_t idx = 0;
  status <<= 4;
  status |= GPIO_ISTAT(GPIOA) & 0x000F;
  switch(idx){
    case 0:
      GPIO_mode(A, 4, GPIO_HIZ); GPIO_mode(A, 5, GPIO_PP50); idx = 1;
      break;
    case 1:
      GPIO_mode(A, 5, GPIO_HIZ); GPIO_mode(A, 6, GPIO_PP50); idx = 2;
      break;
    case 2:
      GPIO_mode(A, 6, GPIO_HIZ); GPIO_mode(A, 7, GPIO_PP50); idx = 3;
      break;
    default:
      GPIO_mode(A, 7, GPIO_HIZ); GPIO_mode(A, 4, GPIO_PP50); idx = 0;
      status_res = status;
      break;
  }
  return status_res;
}
void kbd_init(){
  GPIO_CTL0(GPIOA) = (0x11110000 * GPIO_HIZ) | (0x00001111 * GPIO_PULL);
  GPIO_OCTL(GPIOA) = (GPIO_OCTL(GPIOA) & 0xFF00) | (0b1111 << 4);
}
void mask2disp(uint16_t mask){
  int res = 0;
  while(mask){
    res++;
    mask >>= 1;
  }
  if(res == 0){screen[10] = 0; return;}
  res--;
  screen[10] = seg_code[res];
}



#define CLOCK_FAIL -1
#define CLOCK_HSE 2
#define CLOCK_HSI 1
int8_t clock_max(){
  int8_t res = CLOCK_HSE;
  int i;
  uint32_t tmp;
  RCU_CTL &=~ RCU_CTL_HXTALEN;
  RCU_CTL &=~ RCU_CTL_HXTALSTB;
  RCU_CTL |= RCU_CTL_HXTALEN;
  for(i=0;i<0x0FFF;i++){
    if(RCU_CTL & RCU_CTL_HXTALSTB){i=0x1FFF; break;}
  }
  if(i != 0x1FFF)res = CLOCK_HSI;
  
  tmp = RCU_CFG0;
  tmp &=~(RCU_CFG0_PLLMF | RCU_CFG0_PLLSEL);
  if(res == CLOCK_HSE){ //8MHz
    tmp |= RCU_CFG0_PLLSEL;
    RCU_CFG1 = (RCU_CFG1 & RCU_CFG1_PREDV0) | RCU_PREDV0_DIV2; //8/2 = 4 MHz
  }
  tmp |= RCU_PLL_MUL27; //CK_SYS = 4*27 = 108 MHz
  
  tmp &=~ (RCU_CFG0_AHBPSC | RCU_CFG0_APB1PSC | RCU_CFG0_APB2PSC);
  tmp |= RCU_AHB_CKSYS_DIV1; //AHB = CK_SYS/1 = 108 MHz
  tmp |= RCU_APB1_CKAHB_DIV2; //APB1 = AHB/2 = 54 MHz
  tmp |= RCU_APB2_CKAHB_DIV1; //APB2 = AHB/1 = 108 MHz
  
  RCU_CFG0 = tmp;
  
  RCU_CTL |= RCU_CTL_PLLEN;
  for(i=0;i<0x0FFF;i++){
    if(RCU_CTL & RCU_CTL_PLLSTB){i=0x1FFF; break;}
  }
  if(i != 0x1FFF)return CLOCK_FAIL;
  tmp = RCU_CFG0;
  tmp &=~RCU_CFG0_SCS;
  tmp |= RCU_CKSYSSRC_PLL;
  RCU_CFG0 = tmp;
  for(i=0;i<0x0FFF;i++){
    if((RCU_CFG0 & RCU_CFG0_SCSS)==RCU_SCSS_PLL){i=0x1FFF; break;}
  }
  if(i != 0x1FFF)return CLOCK_FAIL;
  SystemCoreClock = 108000000;
  return res;
}

//datasheet, p.33
//refman, p.222
//PB6 = TIM3.0
//PB8 = TIM3.2 -- в качестве ДЗ будет вывод на PA8 (TIM0.0)
//SBTN = TIM2.2

#define TIM	A,8,1,GPIO_APP50 //TIM0.0

inline uint32_t read_mcycles(){
  uint32_t res;
  asm volatile("csrr %0, mcycle" : "=r"(res) );
  return res;
}

void delay_cycles(uint32_t cycles){
  int32_t cur_cycles, av_cycles;
  av_cycles = read_mcycles() + cycles;
  do{cur_cycles = read_mcycles();}while( (av_cycles - cur_cycles) > 0 );
}

void delay_us(uint32_t us){
  int32_t cur_cycles, av_cycles;
  av_cycles = read_mcycles() + (us * (F_CPU / 1000000));
  do{cur_cycles = read_mcycles();}while( (av_cycles - cur_cycles) > 0 );
}

void delay_ms(uint32_t ms){
  int32_t cur_cycles, av_cycles;
  av_cycles = read_mcycles() + (ms * (F_CPU / 1000 ));
  do{cur_cycles = read_mcycles();}while( (av_cycles - cur_cycles) > 0 );
}

extern const uint8_t adata_start[]   asm(AUDIOSRC "_start");
extern const uint8_t adata_end[]     asm(AUDIOSRC "_end");

int main(){
#if F_CPU == 108000000
  clock_max();
#endif
  eclic_init( ECLIC_NUM_INTERRUPTS );
  RCU_APB2EN |= RCU_APB2EN_PAEN | RCU_APB2EN_PBEN | RCU_APB2EN_AFEN | RCU_APB2EN_USART0EN;
  RCU_APB2EN |= RCU_APB2EN_TIMER0EN;
  
  GPIO_config(USART_TX); GPIO_config(USART_RX);
  GPIO_config(RLED); GPIO_config(GLED); GPIO_config(YLED);
  GPIO_config(RBTN); GPIO_config(SBTN);
  
  screen_init();
  kbd_init();
  
  GPIO_config(TIM); //TODO: важно!
  
  //USART_BAUD(USART0) = 8000000 / 9600;
  USART_BAUD(USART0) = F_CPU / 9600;
  USART_CTL0(USART0) = USART_CTL0_TEN | USART_CTL0_REN | USART_CTL0_UEN;
  uart_putc('>');
  
  TIMER_PSC(TIMER0) = (1 - 1);
  TIMER_CAR(TIMER0) = (256 - 1); // 31250 Hz
  
  TIMER_CH0CV(TIMER0) = 128;
  TIMER_CCHP(TIMER0) = TIMER_CCHP_POEN; //ВАЖНО!
  PM_BITMASK( TIMER_CHCTL0(TIMER0), TIMER_CHCTL0_CH0COMCTL, 0b110 ); //прямой ШИМ
  PM_BITMASK( TIMER_CHCTL0(TIMER0), TIMER_CHCTL0_CH0MS, 0b00 );
  TIMER_CHCTL2(TIMER0) |= TIMER_CHCTL2_CH0EN;
  PM_BITMASK( TIMER_CTL0(TIMER0), TIMER_CTL0_CAM, 0b00 );
  TIMER_CTL0(TIMER0) = TIMER_CTL0_CEN;
  
  
  eclic_global_interrupt_enable();
  
  uint32_t cyc_prev = 0, cyc_cur;
  uint32_t i = 0;
  uint32_t data_size = (adata_end - adata_start);
  uint16_t kbd = 0, kbd_prev = 0;
  while(1){
    TIMER_CH0CV(TIMER0) = adata_start[i];
    i++;
    if(i >= data_size){
      i = 0;
      GPO_T(YLED);
    }
    delay_us(1000000 / 8000);
    GPO_T(RLED);
    screen_update();
    
    kbd = kbd_update();
    mask2disp(kbd);
    if(kbd != kbd_prev){
      uart_b16(kbd);
    }
    kbd_prev = kbd;
    
  }
}

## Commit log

2022-03-20 Add basic Blink code
2022-03-20 Add documents
2022-03-27 Add button to blink code
2022-03-27 Add basic UART example
2022-04-04 Add 'memory sections' example
2022-05-14 Add 4.interrupt example
2022-05-16 Add KiCad project and circuit of devboard
2022-09-07 Add '5.C' example
2022-10-25 Add '6.matrix_keyboard' and '7.matrix_led' examples
2022-10-28 C-code: fix non-initialized global variables
2022-11-04 Fix attribute((naked)) in main
2022-11-12 8.timer
2022-11-18 Add 9.DMA
2022-11-22 Add 10, 11, 12 - multitask examples
2022-12-04 Add Karakatitsa (programmer/debugger) schematics, topology, firmware and keyboard driver
2022-12-05 Karakatitsa: add F103 firmware
2022-12-15 Add example 8.timer
2024-02-17 fix zicsr_zifencei
2024-02-17 Add ch32v303 demo code
2024-02-17 Add ch32 docs
2024-03-06 small fixes
2024-03-06 add gd32 demo code
2024-03-07 Append ch32 demo code: add keyboard and audio
2024-03-07 Add documentation: registers from .svd files
2024-03-21 Fix mtvt and something else
2024-03-24 Fix compilation on ALT linux (via risvc64-linux-gnu-gcc
2024-03-27 ch32.blink: add ASM version
2024-03-29 Kbd_driver: fix configurations
2024-06-13 Update RISC-V specs
2024-06-13 Add 13.FPU
2024-07-26 Add ffmpeg demo
2024-12-04 Add RISC-V core documentation
2024-12-12 Add 4.interrupt_ch32 examples: unified, jump and address table; wch-interrupt-fast mode
2025-01-13 8.timer: Add UTC macro
2025-01-16 Fix start flash address: 0x00000000 -> 0x08000000; This may be imortant when JTAG debugging
2025-02-02 Add v10x, fix v303.ld
2025-02-02 Add DMA examples
2025-02-19 13.FPU: Copy libgcc.a (with software floating point functions to ch32_lib
2025-06-15 14.PMP
2025-07-24 Rename GD32 multitask examples; Add CH32 muntitask examples
2025-07-25 multitask-FreeRTOS: change tasks to previous examples
